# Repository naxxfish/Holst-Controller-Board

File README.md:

# 

A PCB (made in KiCAD) which is suitable for running [Holst Controller](https://github.com/naxxfish/Holst-Controller-Firmware).

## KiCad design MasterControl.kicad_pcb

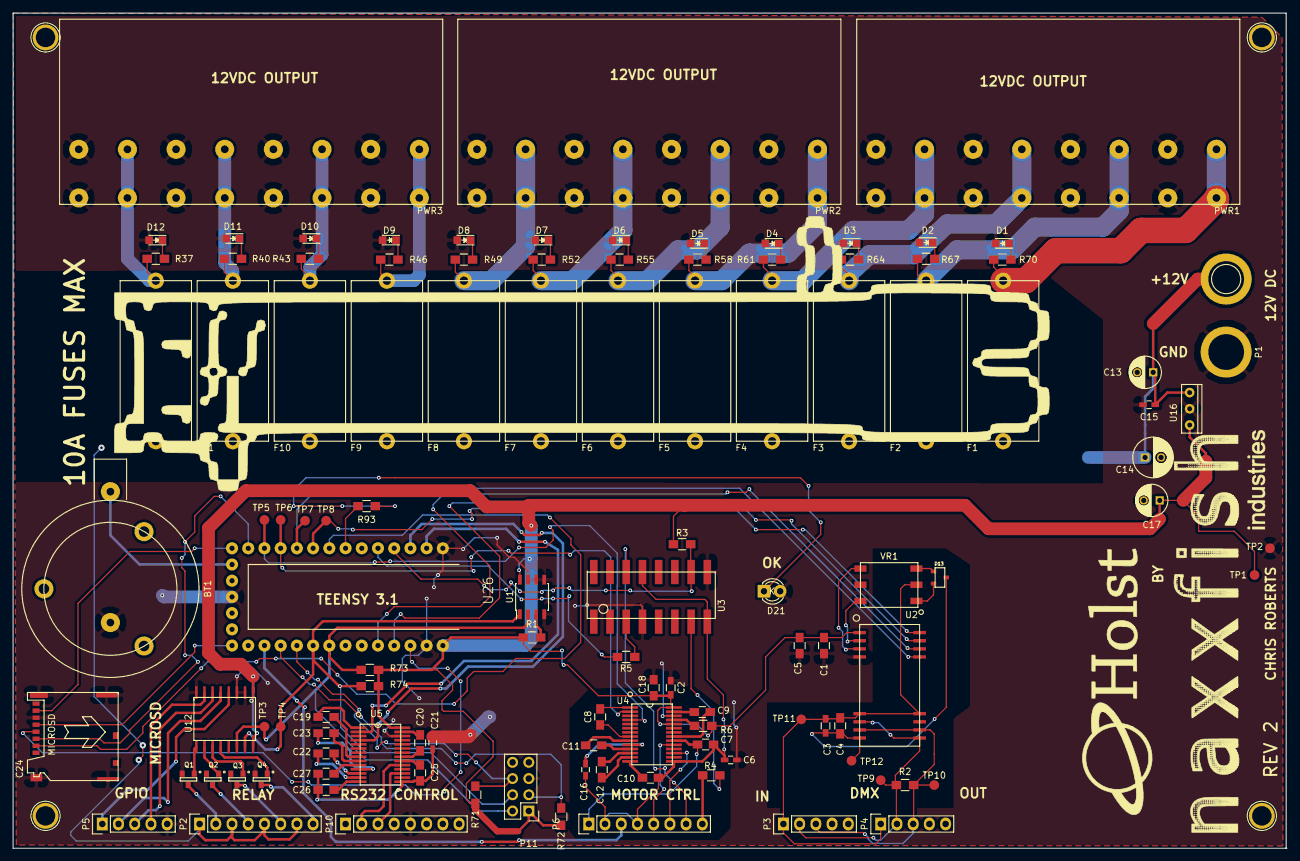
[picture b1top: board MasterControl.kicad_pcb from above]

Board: 2 copper layers, 199.5 x 130.8 mm, 113 parts (0 on the bottom side), 104 nets.

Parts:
BT1: Battery; KEYSTONE-BATT-430-675
C1, C4: 10u; C_0805_HandSoldering
C2, C3: 0.1u; R_0603_HandSoldering
C5: 1U; C_0805_HandSoldering
C6, C21: 10n; C_0603_HandSoldering
C7, C25: 2.2u; C_0805_HandSoldering
C8, C9, C19, C20: 0.047u; C_0805_HandSoldering
C10, C12, C22, C26, C27: 0.47u; C_0805_HandSoldering
C11: 0.1uF; C_0805_HandSoldering
C13: 47uF; C_Radial_D5_L11_P2.5
C14: 100uF; C_Radial_D6.3_L11.2_P2.5
C15: 0.1uF; C_0603_HandSoldering
C16: 0.47u; C_0603_HandSoldering
C17: 2.2uF; C_Radial_D5_L11_P2.5
C18: 1u; C_0805_HandSoldering
C23: 0.1u; C_0805_HandSoldering
C24: SDCARD-SPIMODE; MICROSDCARD-MOLEX-
D1, D2, D3, D4, D5, D6, D7, D8, D9, D10, D11, D12: LED; LED-0805
D13: BAT54C; SOT23-BAT54C
D21: OK; LED-3MM
F1, F2, F3, F4, F5, F6, F7, F8, F9, F10, F11, F12: FUSE; FUSEHOLDER-0031.8211
P1: 12Vin; SolderWirePad_single_2-5mmDrill
P2: RELAYOUT; Pin_Header_Straight_1x08
P3: DMX_IN; Pin_Header_Straight_1x05
P4: DMX_OUT; Pin_Header_Straight_1x05
P5: GPIO; Pin_Header_Straight_1x05
P6: MOTOR_RS232; Pin_Header_Straight_1x08
P10: CONTROL; Pin_Header_Straight_1x08
P11: FRONTPANEL; Pin_Header_Straight_2x04
PWR1: PWROUT1; PHEONIX-1804852
PWR2: PWROUT2; PHEONIX-1804852
PWR3: PWROUT3; PHEONIX-1804852
Q1, Q2, Q3, Q4: MOSFET_N; IRLML2502PBF-SOT23
R1: 1K2; R_0805_HandSoldering
R2: 120R; R_0805_HandSoldering
R3, R6, R71, R72, R73, R74: 10K; R_0805_HandSoldering
R4, R5: 330R; R_0805_HandSoldering
R37, R40, R43, R46, R49, R52, R55, R58, R61, R64, R67, R70: 480; R_0805_HandSoldering
R93: 330; R_0805_HandSoldering
TP1, TP2, TP3, TP4, TP5, TP6, TP7, TP8, TP9, TP10, TP11, TP12: Measurement_Point_Round-SMD-Pad_Small
U1: AT30TS750; SOIC-8_3.9x4.9mm_Pitch1.27mm
U2: MAX3535E; MAXIM-W28M-9
U3: LTV-846S
U4, U5: MAX3250; MAXIM-SSOP28
U12: PCF8574; PCF8574DWR-SOIC16
U16: LF050CV; LF00ABC-TO-220
U26: TEENSY3V1; Teensy-3.1
VR1: TGM-240; TGM-240NS

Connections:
+3V3: C24.4, U26.31
+5V: C1.1, C2.1, C5.2, C17.1, C18.2, P11.1, R1.1, R3.2, R6.2, R71.1, R72.1, R73.1, R74.1, TP1.1, U1.8, U2.1, U4.24, U4.28, U5.28, U12.1, U12.16, U16.3, U26.33
+12V: C13.1, C14.1, C15.1, F1.1, F2.1, F3.1, F4.1, F5.1, F6.1, F7.1, F8.1, F9.1, F10.1, F11.1, F12.1, P2.1, P2.3, P2.5, P2.7, U16.1
/DMX Transciever/DMXGND: C3.2, C4.2, P3.1, P4.1, TP11.1, U2.11, U2.18, VR1.2
/DMX Transciever/DMX_EN: U2.26, U26.29
/DMX Transciever/DMX_RECV_EN: U2.27, U26.30
/DMX Transciever/DMX_RX: TP8.1, U2.28, U26.9
/DMX Transciever/DMX_TX: TP7.1, U2.25, U26.10
/Display/BTN_INT: P11.6, R71.2, U26.24
/Display/ESTOP: P11.3, R72.2, U26.23
/Display/I2C_SCL: P11.2, R73.2, TP3.1, U1.2, U12.14, U26.26
/Display/I2C_SDA: P11.4, R74.2, TP4.1, U1.1, U12.15, U26.25
/GP outputs/B0: Q1.G, U12.9
/GP outputs/B1: Q2.G, U12.10
/GP outputs/B2: Q3.G, U12.11
/GP outputs/B3: Q4.G, U12.12
/GP outputs/GPIO1: P5.1, U12.4
/GP outputs/GPIO2: P5.2, U12.5
/GP outputs/GPIO3: P5.3, U12.6
/GP outputs/GPIO4: P5.4, U12.7
/GP outputs/RELAY1: P2.2, Q1.D
/GP outputs/RELAY2: P2.4, Q2.D
/GP outputs/RELAY3: P2.6, Q3.D
/GP outputs/RELAY4: P2.8, Q4.D
/IOcon/1WIRE: P6.3, U26.22
/IOcon/CTRL_RX_CONN: P10.3, U5.17
/IOcon/CTRL_TX_CONN: P10.2, U5.19
/IOcon/DMXIN+: P3.3, P4.3, R2.2, TP10.1, U2.13, U2.16
/IOcon/DMXIN-: P3.2, P4.2, R2.1, TP9.1, U2.12, U2.15
/IOcon/MC_GND: C6.1, C7.2, C10.2, C16.2, P6.2, P6.4, U3.8, U3.13, U4.15
/Microcontroller/CTRL_RX: U5.2, U26.2
/Microcontroller/CTRL_TX: U5.4, U26.3
/Microcontroller/SPI_MISO: C24.7, U26.14
/Microcontroller/SPI_MOSI: C24.3, U26.13
/Microcontroller/SPI_SCK: C24.5, U26.20
/Motor Control Interface/MC_ERR_IN: P6.8, R4.1
/Motor Control Interface/MC_ERR_READ: R3.1, U3.10, U26.4
/Motor Control Interface/MC_FAULT: R6.1, U4.25
/Motor Control Interface/MC_RST: R5.1, U26.5
/Motor Control Interface/MC_RST_OUT: P6.7, U3.14
/Motor Control Interface/MC_RX: TP6.1, U4.2, U26.11
/Motor Control Interface/MC_RX_OUT: P6.5, U4.19
/Motor Control Interface/MC_TX: TP5.1, U4.4, U26.12
/Motor Control Interface/MC_TX_OUT: P6.6, U4.17
/PowerCircuits/FUSEDPOWER1: F1.2, PWR1.1, R70.2
/PowerCircuits/FUSEDPOWER2: F2.2, PWR1.3, R67.2
/PowerCircuits/FUSEDPOWER3: F3.2, PWR1.5, R64.2
/PowerCircuits/FUSEDPOWER4: F4.2, PWR1.7, R61.2
/PowerCircuits/FUSEDPOWER5: F5.2, PWR2.1, R58.2
/PowerCircuits/FUSEDPOWER6: F6.2, PWR2.3, R55.2
/PowerCircuits/FUSEDPOWER7: F7.2, PWR2.5, R52.2
/PowerCircuits/FUSEDPOWER8: F8.2, PWR2.7, R49.2
/PowerCircuits/FUSEDPOWER9: F9.2, PWR3.1, R46.2
/PowerCircuits/FUSEDPOWER10: F10.2, PWR3.3, R43.2
/PowerCircuits/FUSEDPOWER11: F11.2, PWR3.5, R40.2
/PowerCircuits/FUSEDPOWER12: F12.2, PWR3.7, R37.2
GND: BT1.2, C1.2, C2.2, C5.1, C6.2, C13.2, C14.2, C15.2, C17.2, C18.1, C21.1, C24.6, C24.9, D1.2, D2.2, D3.2, D4.2, D5.2, D6.2, D7.2, D8.2, D9.2, D10.2, D11.2, D12.2, D21.2, P1.1, P5.5, P10.5, P11.5, PWR1.2, PWR1.4, PWR1.6, PWR1.8, PWR2.2, PWR2.4, PWR2.6, PWR2.8, PWR3.2, PWR3.4, PWR3.6, PWR3.8, Q1.S, Q2.S, Q3.S, Q4.S, TP2.1, U1.4, U1.5, U1.6, U1.7, U2.4, U3.4, U3.9, U4.26, U5.26, U12.2, U12.3, U12.8, U16.2, U26.1, U26.17, U26.32
MC_VCC: C7.1, P6.1, U4.20
unnamed: BT1.1, U26.15
unnamed: C3.1, C4.1, D13.3, TP12.1, U2.14
unnamed: C8.1, U4.1
unnamed: C8.2, U4.8
unnamed: C9.1, U4.27
unnamed: C9.2, U4.21
unnamed: C10.1, U4.14
unnamed: C11.1, U4.9
unnamed: C11.2, U4.11
unnamed: C12.1, U4.12
unnamed: C12.2, U4.13
unnamed: C16.1, U4.10
unnamed: C19.1, U5.8
unnamed: C19.2, U5.1
unnamed: C20.1, U5.27
unnamed: C20.2, U5.21
unnamed: C21.2, C25.1, C26.1, C27.1, U5.15
unnamed: C22.1, U5.13
unnamed: C22.2, U5.12
unnamed: C23.1, U5.11
unnamed: C23.2, U5.9
unnamed: C24.2, U26.8
unnamed: C25.2, U5.20
unnamed: C26.2, U5.14
unnamed: C27.2, U5.10
unnamed: D1.1, R70.1
unnamed: D2.1, R67.1
unnamed: D3.1, R64.1
unnamed: D4.1, R61.1
unnamed: D5.1, R58.1
unnamed: D6.1, R55.1
unnamed: D7.1, R52.1
unnamed: D8.1, R49.1
unnamed: D9.1, R46.1
unnamed: D10.1, R43.1
unnamed: D11.1, R40.1
unnamed: D12.1, R37.1
unnamed: D13.1, VR1.3
unnamed: D13.2, VR1.1
unnamed: D21.1, R93.1
unnamed: R1.2, U1.3
unnamed: R4.2, U3.7
unnamed: R5.2, U3.3
unnamed: R93.2, U26.7
unnamed: U2.2, VR1.6
unnamed: U2.3, VR1.4

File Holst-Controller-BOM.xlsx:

Reference | Value | Footprint | Datasheet | RS
R93 | 330.0 | Resistors_SMD:R_0805_HandSoldering |  | 666-2471
R37 | 480.0 | Resistors_SMD:R_0805_HandSoldering |  | 223-0376
R40 | 480.0 | Resistors_SMD:R_0805_HandSoldering |  | 223-0376
R43 | 480.0 | Resistors_SMD:R_0805_HandSoldering |  | 223-0376
R46 | 480.0 | Resistors_SMD:R_0805_HandSoldering |  | 223-0376
R49 | 480.0 | Resistors_SMD:R_0805_HandSoldering |  | 223-0376
R52 | 480.0 | Resistors_SMD:R_0805_HandSoldering |  | 223-0376
R55 | 480.0 | Resistors_SMD:R_0805_HandSoldering |  | 223-0376
R58 | 480.0 | Resistors_SMD:R_0805_HandSoldering |  | 223-0376
R61 | 480.0 | Resistors_SMD:R_0805_HandSoldering |  | 223-0376
R64 | 480.0 | Resistors_SMD:R_0805_HandSoldering |  | 223-0376
R67 | 480.0 | Resistors_SMD:R_0805_HandSoldering |  | 223-0376
R70 | 480.0 | Resistors_SMD:R_0805_HandSoldering |  | 223-0376
C19 | 0.047u | Capacitors_SMD:C_0805_HandSoldering |  | 391-303
C20 | 0.047u | Capacitors_SMD:C_0805_HandSoldering |  | 391-303
C8 | 0.047u | Capacitors_SMD:C_0805_HandSoldering |  | 391-303
C9 | 0.047u | Capacitors_SMD:C_0805_HandSoldering |  | 391-303
C2 | 0.1u | Resistors_SMD:R_0603_HandSoldering |  | 264-4646
C23 | 0.1u | Capacitors_SMD:C_0805_HandSoldering |  | 390-990
C3 | 0.1u | Resistors_SMD:R_0603_HandSoldering |  | 264-4646
C11 | 0.1uF | Capacitors_SMD:C_0805_HandSoldering |  | 390-990
C15 | 0.1uF | Capacitors_SMD:C_0603_HandSoldering |  | 264-4646
C10 | 0.47u | Capacitors_SMD:C_0805_HandSoldering |  | 391-296
C12 | 0.47u | Capacitors_SMD:C_0805_HandSoldering |  | 391-296
C16 | 0.47u | Capacitors_SMD:C_0603_HandSoldering |  | 698-3349
C22 | 0.47u | Capacitors_SMD:C_0603_HandSoldering |  | 698-3349
C26 | 0.47u | Capacitors_SMD:C_0603_HandSoldering |  | 698-3349
C27 | 0.47u | Capacitors_SMD:C_0603_HandSoldering |  | 698-3349
C14 | 100uF | Capacitors_ThroughHole:C_Radial_D6.3_L11.2_P2.5 |  | 475-8769
R3 | 10K | Resistors_SMD:R_0805_HandSoldering |  | 740-9072
R6 | 10K | Resistors_SMD:R_0805_HandSoldering |  | 740-9072
R71 | 10K | Resistors_SMD:R_0805_HandSoldering |  | 740-9072
R72 | 10K | Resistors_SMD:R_0805_HandSoldering |  | 740-9072
R73 | 10K | Resistors_SMD:R_0805_HandSoldering |  | 740-9072
R74 | 10K | Resistors_SMD:R_0805_HandSoldering |  | 740-9072
C21 | 10n | Capacitors_SMD:C_0603_HandSoldering |  | 464-6357
C6 | 10n | Capacitors_SMD:C_0603_HandSoldering |  | 464-6357
C1 | 10u | Capacitors_SMD:C_0805_HandSoldering |  | 698-3544
C4 | 10u | Capacitors_SMD:C_0805_HandSoldering |  | 698-3544
R2 | 120R | Resistors_SMD:R_0805_HandSoldering |  | 566-840
P1 | 12Vin | Wire_Pads:SolderWirePad_single_2-5mmDrill
R1 | 1K2 | Resistors_SMD:R_0805_HandSoldering |  | 565-926
C18 | 1u | Capacitors_SMD:C_0805_HandSoldering |  | 264-4450
C5 | 1U | Capacitors_SMD:C_0805_HandSoldering |  | 264-4450
C25 | 2.2u | Capacitors_SMD:C_0805_HandSoldering |  | 749-2138
C7 | 2.2u | Capacitors_SMD:C_0805_HandSoldering |  | 723-5039
C17 | 2.2uF | Capacitors_ThroughHole:C_Radial_D5_L11_P2.5 |  | 520-1242
R4 | 330R | Resistors_SMD:R_0805_HandSoldering |  | 666-2471
R5 | 330R | Resistors_SMD:R_0805_HandSoldering |  | 666-2471
C13 | 47uF | Capacitors_ThroughHole:C_Radial_D5_L11_P2.5 |  | 475-8882
U1 | AT30TS750 | Housings_SOIC:SOIC-8_3.9x4.9mm_Pitch1.27mm |  | 738-0108
D13 | BAT54C | naxxfish-footprints:SOT23-BAT54C |  | 670-8794
BT1 | Battery | naxxfish-footprints:KEYSTONE-BATT-430-675 |  | 430-675
P10 | CONTROL | Pin_Headers:Pin_Header_Straight_1x08 |  |  | 687-7935
P3 | DMX_IN | Pin_Headers:Pin_Header_Straight_1x05 |  |  | 687-7913
P4 | DMX_OUT | Pin_Headers:Pin_Header_Straight_1x05 |  |  | 687-7913
P11 | FRONTPANEL | Pin_Headers:Pin_Header_Straight_2x04
F1 | FUSE | naxxfish-footprints:FUSEHOLDER-0031.8211 |  | 563-334A | Fuse!
F10 | FUSE | naxxfish-footprints:FUSEHOLDER-0031.8211 |  | 563-334A
F11 | FUSE | naxxfish-footprints:FUSEHOLDER-0031.8211 |  | 563-334A
F12 | FUSE | naxxfish-footprints:FUSEHOLDER-0031.8211 |  | 563-334A
F2 | FUSE | naxxfish-footprints:FUSEHOLDER-0031.8211 |  | 563-334A
F3 | FUSE | naxxfish-footprints:FUSEHOLDER-0031.8211 |  | 563-334A
F4 | FUSE | naxxfish-footprints:FUSEHOLDER-0031.8211 |  | 563-334A
F5 | FUSE | naxxfish-footprints:FUSEHOLDER-0031.8211 |  | 563-334A
F6 | FUSE | naxxfish-footprints:FUSEHOLDER-0031.8211 |  | 563-334A
F7 | FUSE | naxxfish-footprints:FUSEHOLDER-0031.8211 |  | 563-334A
F8 | FUSE | naxxfish-footprints:FUSEHOLDER-0031.8211 |  | 563-334A
F9 | FUSE | naxxfish-footprints:FUSEHOLDER-0031.8211 |  | 563-334A
P5 | GPIO | Pin_Headers:Pin_Header_Straight_1x05 |  |  | 687-7913
D1 | LED | LEDs:LED-0805 |  | 654-5773
D10 | LED | LEDs:LED-0805 |  | 654-5773
D11 | LED | LEDs:LED-0805 |  | 654-5773
D12 | LED | LEDs:LED-0805 |  | 654-5773
D2 | LED | LEDs:LED-0805 |  | 654-5773
D3 | LED | LEDs:LED-0805 |  | 654-5773
D4 | LED | LEDs:LED-0805 |  | 654-5773
D5 | LED | LEDs:LED-0805 |  | 654-5773
D6 | LED | LEDs:LED-0805 |  | 654-5773
D7 | LED | LEDs:LED-0805 |  | 654-5773
D8 | LED | LEDs:LED-0805 |  | 654-5773
D9 | LED | LEDs:LED-0805 |  | 654-5773
U16 | LF050CV | naxxfish-footprints:LF00ABC-TO-220 |  | 355-4257
U3 | LTV-846S | naxxfish-footprints:LTV-846S |  | 691-2230
U4 | MAX3250 | naxxfish-footprints:MAXIM-SSOP28 | http://datasheets.maximintegrated.com/en/ds/MAX3250.pdf | 732-9373
U5 | MAX3250 | naxxfish-footprints:MAXIM-SSOP28 | http://datasheets.maximintegrated.com/en/ds/MAX3250.pdf | 732-9374
U2 | MAX3535E | naxxfish-footprints:MAXIM-W28M-9 |  | 732-9503
P6 | MOTOR_RS232 | Pin_Headers:Pin_Header_Straight_1x08 |  |  | 687-7935
D21 | OK | LEDs:LED-3MM |  | 654-5773
U12 | PCF8574 | naxxfish-footprints:PCF8574DWR-SOIC16 |  | 517-0233
PWR1 | PWROUT1 | naxxfish-footprints:PHEONIX-1804852
PWR2 | PWROUT2 | naxxfish-footprints:PHEONIX-1804852
PWR3 | PWROUT3 | naxxfish-footprints:PHEONIX-1804852
P2 | RELAYOUT | Pin_Headers:Pin_Header_Straight_1x08 |  |  | 687-7935
C24 | SDCARD-SPIMODE | naxxfish-footprints:MICROSDCARD-MOLEX- |  | 880-1277
U26 | TEENSY3V1 | naxxfish-footprints:Teensy-3.1
VR1 | TGM-240 | naxxfish-footprints:TGM-240NS |  | 736-9987

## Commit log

2016-10-23 Added gerbers
2016-10-23 Added BOM
2016-10-23 Added picture of board
2016-10-23 Added readme
